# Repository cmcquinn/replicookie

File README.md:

# Replicookie

KiCad design files for Replicookie, a 3D Printer driver board based around the [Snickerdoodle](https://krtkl.com/snickerdoodle/) development board.

This project is open-source hardware, licensed under the CERN 1.2 license.

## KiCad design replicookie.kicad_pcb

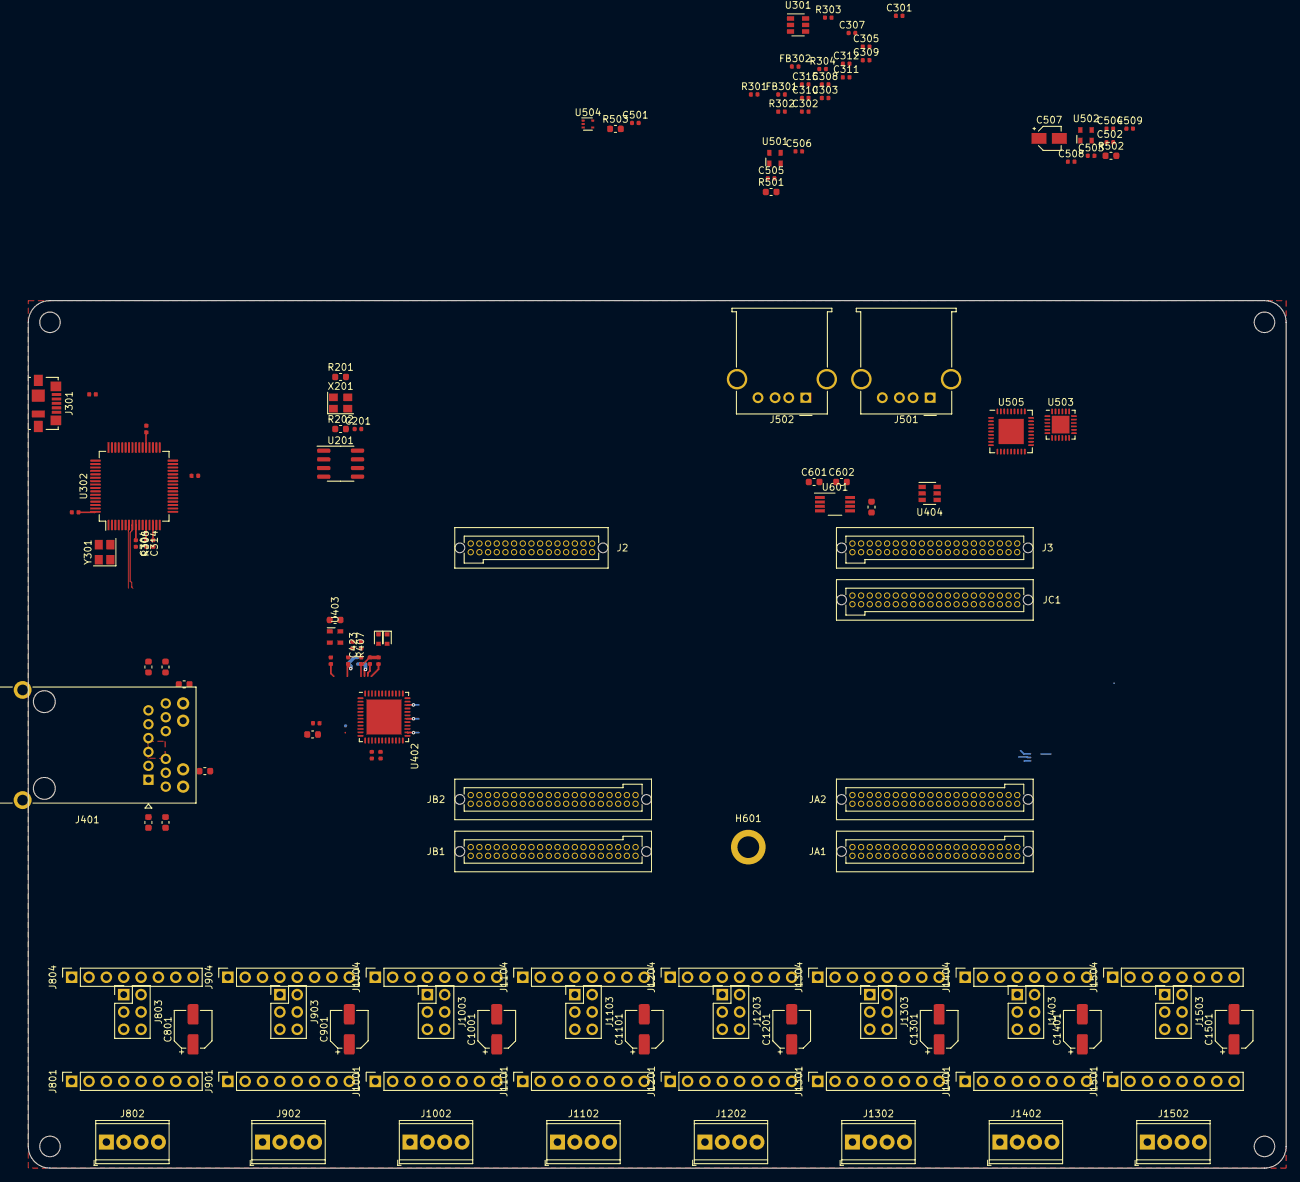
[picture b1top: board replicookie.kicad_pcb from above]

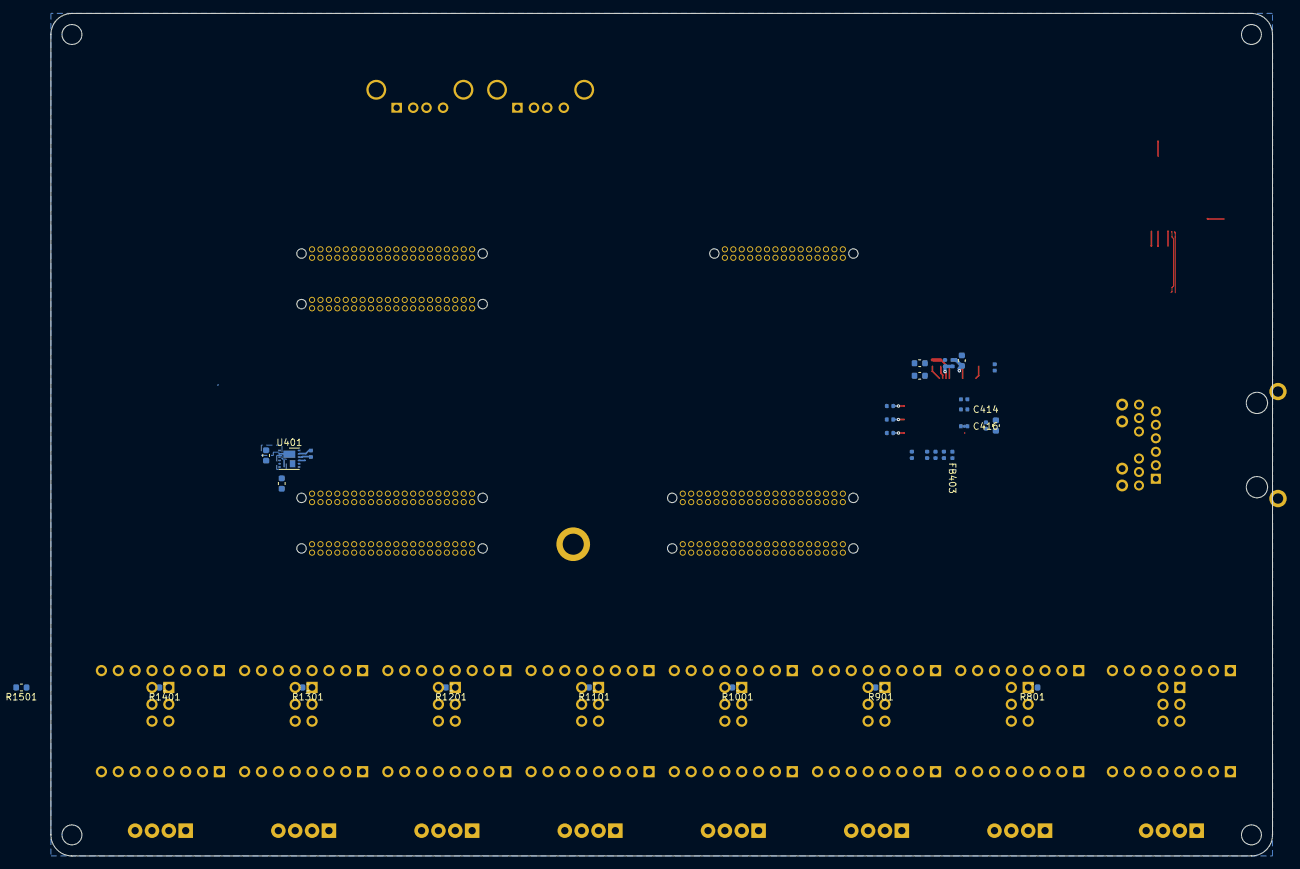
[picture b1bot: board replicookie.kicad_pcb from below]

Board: 4 copper layers, 184.1 x 127.0 mm, 163 parts (31 on the bottom side), 169 nets.

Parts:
C201, C501, C502: 0.01u; C_0402_1005Metric
C301, C303: 27p; C_0402_1005Metric
C302, C307, C308, C309, C310, C311, C312, C313, C314, C315, C408, C409, C410, C411, C412, C413, C414, C415, C416, C417, C418, C419, C420, C421, C504, C505, C508, C509: 0.1u; C_0402_1005Metric
C304, C305: 4.7u; C_0402_1005Metric
C306: 3.3u; C_0402_1005Metric
C401: 4.7u; C_0603_1608Metric
C402: 560p; C_0402_1005Metric
C403, C404, C405, C406, C407, C424: 10u; C_0603_1608Metric
C422: 0.01u; C_0603_1608Metric
C423: 10u; C_0402_1005Metric
C425, C426, C427, C428, C429, C601, C602: 0.1u; C_0603_1608Metric
C503, C506: 1u; C_0402_1005Metric
C507: 150u; CP_Elec_3x5.3
C801, C901, C1001, C1101, C1201, C1301, C1401, C1501: 100u 35V; CP_Elec_5x3
D401, D402: 1N4148WT; D_SOD-523
FB301, FB302: 80 ohm 100 MHz; L_0402_1005Metric
FB401, FB402, FB403: 100 ohms; L_0402_1005Metric
H101, H102, H103, H104: MountingHole; MountingHole_3mm
H601: MountingHole; Snickerdoodle_Mounting_Hole
J2: TFM-115-01-F-D-A; Samtec_TFM-115-01-F-D-A_2x15_P1.27mm_Horizontal
J3: TFM-120-01-F-D-A; Samtec_TFM-120-01-F-D-A_2x20_P1.27mm_Horizontal
J301: USB_B_Micro; USB_Micro-B_Molex_47346-0001
J401: JK0654219; RJ45_Pulse_JK0654219NL_Horizontal
J501, J502: USB_A; USB_A_Molex_67643_Horizontal
J801, J804, J901, J904, J1001, J1004, J1101, J1104, J1201, J1204, J1301, J1304, J1401, J1404, J1501, J1504: Conn_01x08_Female; PinSocket_1x08_P2.54mm_Vertical
J802, J902, J1002, J1102, J1202, J1302, J1402, J1502: Screw_Terminal_01x04; TerminalBlock_Phoenix_MPT-0,5-4-2.54_1x04_P2.54mm_Horizontal
J803, J903, J1003, J1103, J1203, J1303, J1403, J1503: Conn_02x03_Odd_Even; PinHeader_2x03_P2.54mm_Vertical
JA1, JA2: TFM-120-01-F-D-A; Samtec_TFM-120-01-F-D-A_2x20_P1.27mm_Horizontal
JB1, JB2: TFM-120-01-F-D-A; Samtec_TFM-120-01-F-D-A_2x20_P1.27mm_Horizontal
JC1: TFM-120-01-F-D-A; Samtec_TFM-120-01-F-D-A_2x20_P1.27mm_Horizontal
R201, R202: 2k; R_0603_1608Metric
R301, R302, R304, R401, R407: 10k; R_0402_1005Metric
R303: 2k; R_0402_1005Metric
R305: 12k; R_0402_1005Metric
R306, R403, R405: 1k; R_0402_1005Metric
R307: 470; R_0402_1005Metric
R402: 4.7k; R_0402_1005Metric
R404: 1.5k; R_0402_1005Metric
R406: 12.1k; R_0402_1005Metric
R408, R409: 75; R_0603_1608Metric
R501: 8.06k 1%; R_0603_1608Metric
R502: 10k 1/16W; R_0603_1608Metric
R503: 12k; R_0603_1608Metric
R801, R901, R1001, R1101, R1201, R1301, R1401, R1501: 10k; R_0603_1608Metric
U201: DS1307ZN+; SOIC-8_3.9x4.9mm_P1.27mm
U301: 93LCxxBxxOT; SOT-23-6
U302: FT4232H; LQFP-64_10x10mm_P0.5mm
U401: MIC33050-4YHL; HDFN-12-1EP_3x3mm_P0.5mm_EP1.8x1.125mm
U402: KSZ9031RNXCA; QFN-48-1EP_7x7mm_P0.5mm_EP5.15x5.15mm
U403: ASDMB-25.000MHz; Oscillator_SMD_Abracon_ASDMB-4Pin_2.5x2.0mm
U404: 74LVC2G07; SOT-23-6
U501: ASDMB-24.000MHz-C; Oscillator_SMD_Abracon_ASDMB-4Pin_2.5x2.0mm
U502: ASDMB-26.000MHz-C; Oscillator_SMD_Abracon_ASDMB-4Pin_2.5x2.0mm
U503: USB3343; QFN-24-1EP_4x4mm_P0.5mm_EP2.6x2.6mm
U504: 74LVC1G07; SOT-553
U505: USB2514B_Bi; QFN-36-1EP_6x6mm_P0.5mm_EP3.7x3.7mm
U601: TCA9800; VSSOP-8_3.0x3.0mm_P0.65mm
X201: ASE-xxxMHz; Oscillator_SMD_Abracon_ASE-4Pin_3.2x2.5mm
Y301: ABM8-12.000MHZ-20; Crystal_SMD_Abracon_ABM8G-4Pin_3.2x2.5mm

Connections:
+1V8: C501.1, C502.1, C601.2, U501.1 (Standby), U501.4 (VDD), U502.1 (Standby), U502.4 (VDD), U504.5 (VCC), U601.1 (VCCA)
+3V3: C201.1, C309.1, C310.1, C311.1, C312.1, C401.1, C405.1, C408.1, C409.1, C410.1, C422.1, C429.1, C602.2, D401.1 (K), FB301.2, FB302.2, FB403.1, J801.2, J803.1, J803.2, J901.2, J903.1, J903.2, J1001.2, J1003.1, J1003.2, J1101.2, J1103.1, J1103.2, J1201.2, J1203.1, J1203.2, J1301.2, J1303.1, J1303.2, J1401.2, J1403.1, J1403.2, J1501.2, J1503.1, J1503.2, R201.1, R202.1, R301.1, R302.1, R304.1, R306.1, R401.1, R402.1, R404.1, R407.1, R408.2, R409.2, R801.1, R901.1, R1001.1, R1101.1, R1201.1, R1301.1, R1401.1, R1501.1, U201.8 (VCC), U302.20 (VCCIO), U302.31 (VCCIO), U302.42 (VCCIO), U302.50 (VREGIN), U302.56 (VCCIO), U401.1 (VIN), U401.9 (EN), U402.16 (DVDDH), U402.34 (DVDDH), U402.40 (DVDDH), U403.1 (Standby), U403.4 (VDD), U404.5 (VCC), U505.27 (VBUS_DET), U601.8 (VCCB), X201.1 (EN), X201.4 (Vdd)
+24V: C801.1, C901.1, C1001.1, C1101.1, C1201.1, C1301.1, C1401.1, C1501.1, J801.8, J901.8, J1001.8, J1101.8, J1201.8, J1301.8, J1401.8, J1501.8
/DRV0_CTRL.~EN: J804.8, R801.2
/DRV1_CTRL.~EN: J904.8, R901.2
/DRV2_CTRL.~EN: J1004.8, R1001.2
/DRV3_CTRL.~EN: J1104.8, R1101.2
/DRV4_CTRL.~EN: J1204.8, R1201.2
/DRV5_CTRL.~EN: J1304.8, R1301.2
/DRV6_CTRL.~EN: J1404.8, R1401.2
/DRV7_CTRL.~EN: J1504.8, R1501.2
/ETHERNET.MDC: JB2.37, U402.36 (MDC)
/ETHERNET.MDIO: JB2.35, R404.2, U402.37 (MDIO)
/ETHERNET.RXD0: JB2.30, U402.32 (RXD0/MODE0)
/ETHERNET.RXD1: JB2.26, U402.31 (RXD1/MODE1)
/ETHERNET.RXD2: JB2.24, U402.28 (RXD2/MODE2)
/ETHERNET.RXD3: JB2.20, U402.27 (RXD3/MODE3)
/ETHERNET.RX_CLK: JB2.36, U402.35 (RX_CLK/PHYAD2)
/ETHERNET.RX_CTL: JB2.32, U402.33 (RX_DV/CLK125_EN)
/ETHERNET.TXD0: JB2.4, U402.19 (TXD0)
/ETHERNET.TXD1: JB2.6, U402.20 (TXD1)
/ETHERNET.TXD2: JB2.8, U402.21 (TXD2)
/ETHERNET.TXD3: JB2.12, U402.22 (TXD3)
/ETHERNET.TX_CLK: JB2.14, U402.24 (GTX_CLK)
/ETHERNET.TX_CTL: JB2.18, U402.25 (TX_EN)
/Ethernet/25MHZ_CLK: U402.46 (XI), U403.3 (Out)
/Ethernet/AVDDH: C411.1, C412.1, C424.1, FB403.2, U402.1 (AVDDH), U402.12 (AVDDH)
/Ethernet/AVDDL: C406.1, C414.1, C416.1, FB401.1, U402.4 (AVDDL), U402.9 (AVDDL)
/Ethernet/AVDDL_PLL: C407.1, C417.1, FB402.1, U402.44 (AVDDL_PLL)
/Ethernet/CFF: C402.2, U401.11 (CFF)
/Ethernet/CT1: C428.1, J401.12 (MXCT1)
/Ethernet/CT2: C427.1, J401.6 (MXCT2)
/Ethernet/CT3: C426.1, J401.1 (MXCT3)
/Ethernet/CT4: C425.1, J401.7 (MXCT4)
/Ethernet/DVDDL: C402.1, C403.1, C404.1, C413.1, C415.1, C418.1, C419.1, C420.1, C421.1, FB401.2, FB402.2, U401.7 (VOUT), U401.8 (VOUT), U401.10 (SNS), U402.14 (DVDDL), U402.18 (DVDDL), U402.23 (DVDDL), U402.26 (DVDDL), U402.30 (DVDDL), U402.39 (DVDDL)
/Ethernet/ISET: R406.1, U402.48 (ISET)
/Ethernet/LED1: R403.1, U402.17 (LED1/PHAD0/PME_N1), U404.1
/Ethernet/LED1A: J401.16 (LED1+), R409.1
/Ethernet/LED1K: J401.15 (LED1-), U404.6
/Ethernet/LED2: R405.1, U402.15 (LED2/PHYAD1), U404.3
/Ethernet/LED2A: J401.14 (LED2+), R408.1
/Ethernet/LED2K: J401.13 (LED2-), U404.4
/Ethernet/LED_MODE: R401.2, U402.41 (CLK125_NDO/LED_MODE)
/Ethernet/TXRXA+: J401.11 (MX1+), U402.2 (TXRXP_A)
/Ethernet/TXRXA-: J401.10 (MX1-), U402.3 (TXRXM_A)
/Ethernet/TXRXB+: J401.4 (MX2+), U402.5 (TXRXP_B)
/Ethernet/TXRXB-: J401.5 (MX2-), U402.6 (TXRXM_B)
/Ethernet/TXRXC+: J401.3 (MX3+), U402.7 (TXRXP_C)
/Ethernet/TXRXC-: J401.2 (MX3-), U402.8 (TXRXM_C)
/Ethernet/TXRXD+: J401.8 (MX4+), U402.10 (TXRXP_D)
/Ethernet/TXRXD-: J401.9 (MX4-), U402.11 (TXRXM_D)
/Ethernet/~ENET_RST: C423.1, D401.2 (A), D402.2 (A), R407.2, U402.42 (RESET_N)
/Ethernet/~INT~/~PME2: R402.2, U402.38 (INT_N/PME_N2)
/FTDI/D+: J301.3 (D+), U302.8 (DP)
/FTDI/D-: J301.2 (D-), U302.7 (DM)
/FTDI/EECLK: R301.2, U301.4 (CLK), U302.62 (EECLK)
/FTDI/EECS: R304.2, U301.5 (CS), U302.63 (EECS)
/FTDI/EEDATA: R303.1, U301.3 (DI), U302.61 (EEDATA)
/FTDI/EEDO: R302.2, R303.2, U301.1 (DO)
/FTDI/FTDI_1V8: C306.1, C313.1, C314.1, C315.1, U302.12 (VCORE), U302.37 (VCORE), U302.49 (VREGOUT), U302.64 (VCORE)
/FTDI/OSCI: C301.2, U302.2 (OSCI), Y301.3
/FTDI/OSCO: C303.1, U302.3 (OSCO), Y301.1
/FTDI/REF: R305.1, U302.6 (REF)
/FTDI/VPHY: C305.1, C308.1, FB302.1, U302.4 (VPHY)
/FTDI/VPLL: C304.1, C307.1, FB301.1, U302.9 (VPLL)
/FTDI/~FTDI_RESET: R306.2, U302.14 (~RESET)
/MCU_~RST: J2.17, U302.29 (BDBUS3)
/MotorDrivers/Driver0/ADDR0: J803.4, J804.7
/MotorDrivers/Driver0/ADDR1: J803.3, J804.6
/MotorDrivers/Driver0/M1A: J801.4, J802.2
/MotorDrivers/Driver0/M1B: J801.3, J802.1
/MotorDrivers/Driver0/M2A: J801.5, J802.3
/MotorDrivers/Driver0/M2B: J801.6, J802.4
/MotorDrivers/Driver1/ADDR0: J903.4, J904.7
/MotorDrivers/Driver1/ADDR1: J903.3, J904.6
/MotorDrivers/Driver1/M1A: J901.4, J902.2
/MotorDrivers/Driver1/M1B: J901.3, J902.1
/MotorDrivers/Driver1/M2A: J901.5, J902.3
/MotorDrivers/Driver1/M2B: J901.6, J902.4
/MotorDrivers/Driver2/ADDR0: J1003.4, J1004.7
/MotorDrivers/Driver2/ADDR1: J1003.3, J1004.6
/MotorDrivers/Driver2/M1A: J1001.4, J1002.2
/MotorDrivers/Driver2/M1B: J1001.3, J1002.1
/MotorDrivers/Driver2/M2A: J1001.5, J1002.3
/MotorDrivers/Driver2/M2B: J1001.6, J1002.4
/MotorDrivers/Driver3/ADDR0: J1103.4, J1104.7
/MotorDrivers/Driver3/ADDR1: J1103.3, J1104.6
/MotorDrivers/Driver3/M1A: J1101.4, J1102.2
/MotorDrivers/Driver3/M1B: J1101.3, J1102.1
/MotorDrivers/Driver3/M2A: J1101.5, J1102.3
/MotorDrivers/Driver3/M2B: J1101.6, J1102.4
/MotorDrivers/Driver4/ADDR0: J1203.4, J1204.7
/MotorDrivers/Driver4/ADDR1: J1203.3, J1204.6
/MotorDrivers/Driver4/M1A: J1201.4, J1202.2
/MotorDrivers/Driver4/M1B: J1201.3, J1202.1
/MotorDrivers/Driver4/M2A: J1201.5, J1202.3
/MotorDrivers/Driver4/M2B: J1201.6, J1202.4
/MotorDrivers/Driver5/ADDR0: J1303.4, J1304.7
/MotorDrivers/Driver5/ADDR1: J1303.3, J1304.6
/MotorDrivers/Driver5/M1A: J1301.4, J1302.2
/MotorDrivers/Driver5/M1B: J1301.3, J1302.1
/MotorDrivers/Driver5/M2A: J1301.5, J1302.3
/MotorDrivers/Driver5/M2B: J1301.6, J1302.4
/MotorDrivers/Driver6/ADDR0: J1403.4, J1404.7
/MotorDrivers/Driver6/ADDR1: J1403.3, J1404.6
/MotorDrivers/Driver6/M1A: J1401.4, J1402.2
/MotorDrivers/Driver6/M1B: J1401.3, J1402.1
/MotorDrivers/Driver6/M2A: J1401.5, J1402.3
/MotorDrivers/Driver6/M2B: J1401.6, J1402.4
/MotorDrivers/Driver7/ADDR0: J1503.4, J1504.7
/MotorDrivers/Driver7/ADDR1: J1503.3, J1504.6
/MotorDrivers/Driver7/M1A: J1501.4, J1502.2
/MotorDrivers/Driver7/M1B: J1501.3, J1502.1
/MotorDrivers/Driver7/M2A: J1501.5, J1502.3
/MotorDrivers/Driver7/M2B: J1501.6, J1502.4
/RealTimeClock/REF_CLK: U201.1 (X1), X201.3 (OUT)
/SMB_I2C0.SCL: JA1.39, R201.2, U201.6 (SCL)
/SMB_I2C0.SDA: JA1.40, R202.2, U201.5 (SDA)
/SWCLK: J2.15, U302.26 (BDBUS0)
/SWDIO: J2.16, R307.2, U302.28 (BDBUS2)
/Snickerdoodle/SCL: J3.8, U601.2 (SCLA)
/TCK: J2.21, U302.16 (ADBUS0)
/TDI: J2.22, U302.17 (ADBUS1)
/TDO: J2.24, U302.18 (ADBUS2)
/TMS: J2.23, U302.19 (ADBUS3)
/UART0: J804.4, J904.4, J1004.4, J1104.4
/UART1: J1204.4, J1304.4, J1404.4, J1504.4
/USB.CLK: J3.35, U503.2 (CLKOUT)
/USB.DATA0: J3.29, U503.4 (DATA0)
/USB.DATA1: J3.31, U503.5 (DATA1)
/USB.DATA2: J3.32, U503.6 (DATA2)
/USB.DATA3: J3.30, U503.7 (DATA3)
/USB.DATA4: J3.23, U503.8 (DATA4)
/USB.DATA5: J3.37, U503.10 (DATA5)
/USB.DATA6: J3.38, U503.11 (DATA6)
/USB.DATA7: J3.36, U503.12 (DATA7)
/USB.DIR: J3.25, U503.1 (DIR)
/USB.NXT: J3.24, U503.3 (NXT)
/USB.STP: J3.26, U503.24 (STP)
/USB/D1N: J501.2 (D-), U505.2 (USBDP_DN1/PRT_DIS_P1)
/USB/D1P: J501.3 (D+), U505.1 (USBDM_DN1/PRT_DIS_M1)
/USB/D2N: J502.2 (D-), U505.4 (USBDP_DN2/PRT_DIS_P2)
/USB/D2P: J502.3 (D+), U505.3 (USBDM_DN2/PRT_DIS_M2)
/USB/DM: U503.14 (DM), U505.30 (USBDM_UP)
/USB/DP: U503.13 (DP), U505.31 (USBDP_UP)
/USB/REFCLK: U502.3 (Out), U503.21 (REFCLK/XI)
/USB/VBUS: R502.1, U503.17 (VBUS)
/USB/VBUS_OUT: C507.1, R502.2
/USB/VDD33: C506.1, U503.15 (VDD33), U503.18 (ID)
/USB/~HUB_RESET: U504.4, U505.26 (RESET_N)
/ZYNQ_~RST: J2.19, U302.21 (ADBUS4)
/~ETHERNET_RST: D402.1 (K), JB2.38
/~USB_RST: U503.22 (~RESETB), U504.2
BANKA_VIO: JA1.3, JA2.3
BANKB_VIO: JB1.3, JB2.3
BANKC_VIO: J3.3, JC1.3
GND: C201.2, C301.1, C302.2, C303.2, C304.2, C305.2, C306.2, C307.2, C308.2, C309.2, C310.2, C311.2, C312.2, C313.2, C314.2, C315.2, C401.2, C403.2, C404.2, C405.2, C406.2, C407.2, C408.2, C409.2, C410.2, C411.2, C412.2, C413.2, C414.2, C415.2, C416.2, C417.2, C418.2, C419.2, C420.2, C421.2, C422.2, C423.2, C424.2, C425.2, C426.2, C427.2, C428.2, C429.2, C503.2, C504.2, C505.2, C506.2, C507.2, C508.2, C509.2, C601.1, C602.1, C801.2, C901.2, C1001.2, C1101.2, C1201.2, C1301.2, C1401.2, C1501.2, J2.5, J2.6, J2.9, J2.10, J2.20, J2.27, J2.28, J3.9, J3.10, J3.15, J3.16, J3.21, J3.22, J3.27, J3.28, J3.33, J3.34, J301.5 (GND), J301.6 (Shield), J401.SH, J803.5, J803.6, J903.5, J903.6, J1003.5, J1003.6, J1103.5, J1103.6, J1203.5, J1203.6, J1303.5, J1303.6, J1403.5, J1403.6, J1503.5, J1503.6, JA1.9, JA1.10, JA1.15, JA1.16, JA1.21, JA1.22, JA1.27, JA1.28, JA1.33, JA1.34, JA2.9, JA2.10, JA2.15, JA2.16, JA2.21, JA2.22, JA2.27, JA2.28, JA2.33, JA2.34, JB1.9, JB1.10, JB1.15, JB1.16, JB1.21, JB1.22, JB1.27, JB1.28, JB1.33, JB1.34, JB2.9, JB2.10, JB2.15, JB2.16, JB2.21, JB2.22, JB2.27, JB2.28, JB2.33, JB2.34, JC1.9, JC1.10, JC1.15, JC1.16, JC1.21, JC1.22, JC1.27, JC1.28, JC1.33, JC1.34, R305.2, R403.2, R405.2, R406.2, R501.2, R503.2, U201.4 (GND), U301.2 (GND), U302.1 (GND), U302.5 (GND), U302.10 (AGND), U302.11 (GND), U302.13 (TEST), U302.15 (GND), U302.25 (GND), U302.35 (GND), U302.47 (GND), U302.51 (GND), U401.2 (PGND), U401.12 (AGND), U401.13 (EP), U402.29 (VSS), U402.49 (PAD_GND), U403.2 (GND), U404.2 (GND), U503.25 (GND), U504.3 (GND), U505.37 (VSS), U601.4 (GND), X201.2 (GND), Y301.2, Y301.4
unnamed: C302.1, U301.6 (VCC)
unnamed: C501.2, U501.2 (GND)
unnamed: C502.2, U502.2 (GND)
unnamed: C503.1, C504.1, U503.9 (VDDIO), U503.23 (VDD18)
unnamed: C505.1, U503.16 (VBAT)
unnamed: C508.1, U505.34 (PLLFILT)
unnamed: C509.1, U505.14 (CRFILT)
unnamed: R307.1, U302.27 (BDBUS1)
unnamed: R501.1, U503.19 (RBIAS)
unnamed: R503.1, U505.35 (RBIAS)
unnamed: U401.3 (SW), U401.4 (SW), U401.5 (SW), U401.6 (SW)
ZYNQ_VIN: J2.29, J2.30

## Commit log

2020-06-25 Initial commit with template and motor drivers
2020-06-25 Increase text size, redo bus labels
2020-06-25 Configure driver chip address with jumpers
2020-06-25 Add RTC
2020-07-06 Working on gigabit ethernet PHY
2020-07-06 Add links to documentation
2020-07-08 WIre Ethernet PHY
2020-07-08 Finish ethernet sheet, update power calculations
2020-07-08 Annotate schematic
2020-07-10 Add ULPI USB PHY
2020-07-11 Fix footprint associations, use 74LVC2G07 instead of MOSFETs
2020-07-12 Connect Ethernet and USB to MIO, start layout
2020-07-14 Place motor drivers, start layout of Ethernet PHY
2020-07-15 Add FTDI chip
2020-07-15 Add gitignore
2020-07-15 Remove temporary files
2020-07-26 Connect Ethernet PHY to FPGA, route RGMII signals
2020-08-05 Attach ethernet to PL, layout and route
2020-08-08 Move Ethernet around to save space
2020-08-25 Expand PCB, change to inches, center Snickerdoodle
2020-09-16 Move Ethernet PHY to left side of board
2020-10-18 Route RGMII signals
2020-10-20 Route Ethernet differential pairs
2020-10-29 Layout Ethernet PHY decoupling capacitors
2020-10-29 Setup git filters h/t https://jnavila.github.io/plotkicadsch/
2020-10-30 Add filled zones for Ethernet power
2020-10-31 Switch to stacked USB ports
2020-10-31 Ethernet: Route missing track
2020-10-31 Layout Ethernet core power regulator
2020-11-06 Layout Ethernet clock and pull-up resistors
2020-11-06 Finish Ethernet layout
2020-11-08 Route ULPI signals
2020-11-08 Repo cleanup
2020-11-09 Add README.md and LICENSE.md
2020-11-09 Connect USB clock generators to gnd, add clock termination resistor
2020-11-11 Power USB REFCLK from PHY regulator, add pull up resistors to USB reset line
2020-11-25 WIP: layout USB host interface
2021-01-06 Switch to 6 layer stackup, route ULPI
